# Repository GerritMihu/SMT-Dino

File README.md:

# SMT-Dino
 Blinkender Dinosaurier mit dem 14-Bit Zähler 74HCT4060

## Automatisch generierte Files für Doku mit Kibot

## 0402er LED's als Challenge

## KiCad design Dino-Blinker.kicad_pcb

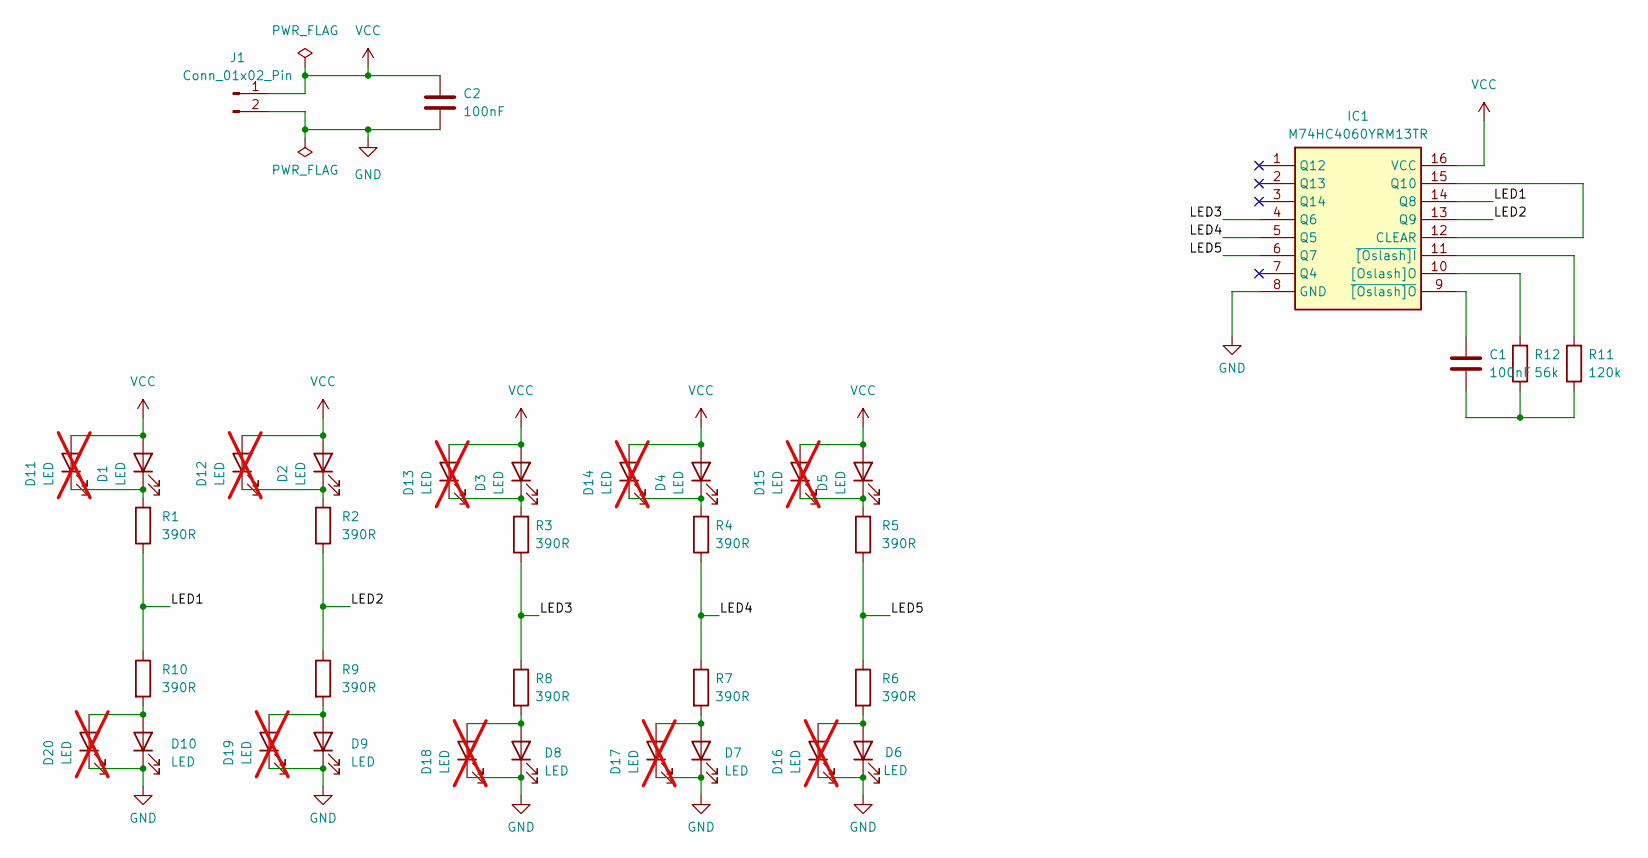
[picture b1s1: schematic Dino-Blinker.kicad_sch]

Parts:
C1, C2: 100nF; C_0805_2012Metric_Pad1.18x1.45mm_HandSolder
D1, D2, D3, D4, D5, D6, D7, D8, D9, D10: LED; LED_0805_2012Metric_Pad1.15x1.40mm_HandSolder
D11, D12, D13, D14, D15, D16, D17, D18, D19, D20: LED; LED_0402_1005Metric_Pad0.77x0.64mm_HandSolder; not fitted
IC1: M74HC4060YRM13TR; SOIC-16_3.9x9.9mm_P1.27mm; Manufacturer_Part_Number M74HC4060YRM13TR; Mouser Part Number 511-M74HC4060YRM13TR
J1: Conn_01x02_Pin; PinHeader_1x02_P2.54mm_Vertical
R1, R2, R3, R4, R5, R6, R7, R8, R9, R10: 390R; R_1206_3216Metric_Pad1.30x1.75mm_HandSolder
R11: 120k; R_1206_3216Metric_Pad1.30x1.75mm_HandSolder
R12: 56k; R_1206_3216Metric_Pad1.30x1.75mm_HandSolder

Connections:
/LED1: IC1.14 (Q8), R1.1, R10.1
/LED2: IC1.13 (Q9), R2.1, R9.1
/LED3: IC1.4 (Q6), R3.1, R8.1
/LED4: IC1.5 (Q5), R4.1, R7.1
/LED5: IC1.6 (Q7), R5.1, R6.1
GND: C2.2, D6.1 (K), D7.1 (K), D8.1 (K), D9.1 (K), D10.1 (K), D16.1 (K), D17.1 (K), D18.1 (K), D19.1 (K), D20.1 (K), IC1.8 (GND), J1.2
unnamed: C1.1, R11.1, R12.1
unnamed: D1.1 (K), D11.1 (K), R1.2
unnamed: D10.2 (A), D20.2 (A), R10.2
unnamed: D2.1 (K), D12.1 (K), R2.2
unnamed: D3.1 (K), D13.1 (K), R3.2
unnamed: D4.1 (K), D14.1 (K), R4.2
unnamed: D5.1 (K), D15.1 (K), R5.2
unnamed: D6.2 (A), D16.2 (A), R6.2
unnamed: D7.2 (A), D17.2 (A), R7.2
unnamed: D8.2 (A), D18.2 (A), R8.2
unnamed: D9.2 (A), D19.2 (A), R9.2
unnamed: IC1.12 (CLEAR), IC1.15 (Q10)
unnamed: IC1.10 ([Oslash]O), R12.2
unnamed: IC1.11 (~[Oslash]I), R11.2
unnamed: C1.2, IC1.9 (~[Oslash]O)
VCC: C2.1, D1.2 (A), D2.2 (A), D3.2 (A), D4.2 (A), D5.2 (A), D11.2 (A), D12.2 (A), D13.2 (A), D14.2 (A), D15.2 (A), IC1.16 (VCC), J1.1

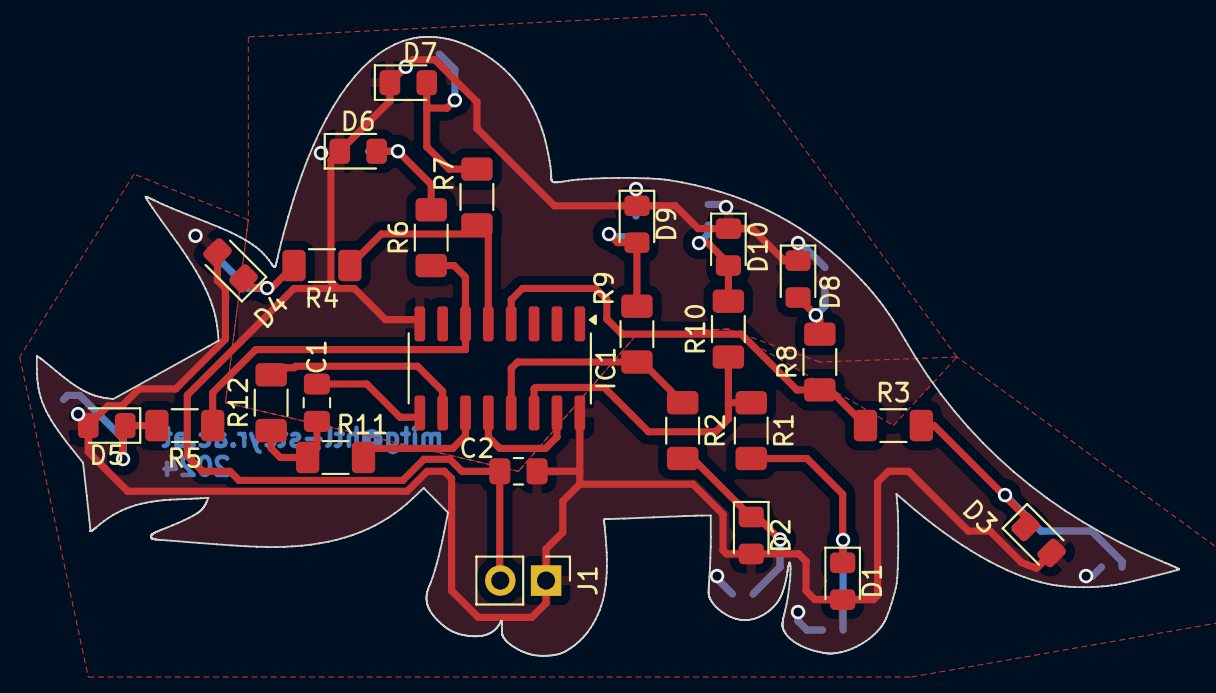
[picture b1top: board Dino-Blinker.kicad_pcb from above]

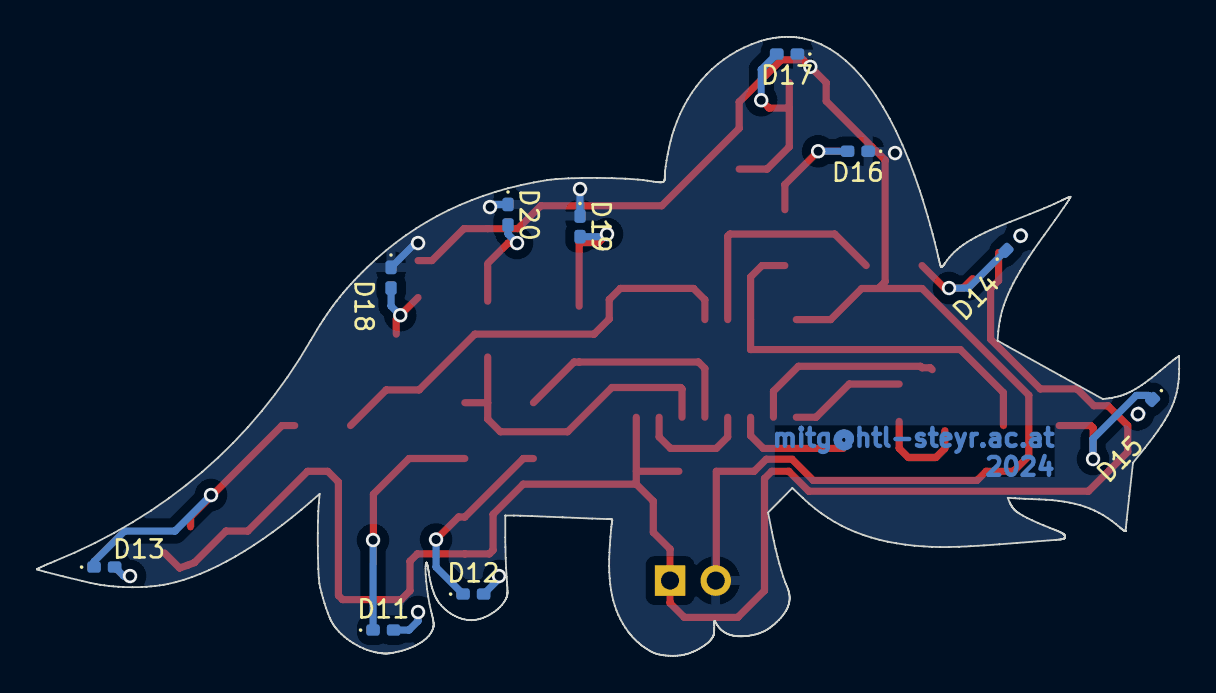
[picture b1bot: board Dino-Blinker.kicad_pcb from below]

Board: 2 copper layers, 63.5 x 34.4 mm, 36 parts (10 on the bottom side), 22 nets.

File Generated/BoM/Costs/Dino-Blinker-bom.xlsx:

|  | KiBot Bill of Materials
 |  | Schematic: | Dino-Blinker | Component Groups: | 7
 |  | Variant: | default | Component Count: | 26 (25 SMD/ 1 THT)
 |  | Revision: |  | Fitted Components: | 26 (25 SMD/ 1 THT)
 |  | Date: | 2024-12-11_00-15-44 | Number of PCBs: | 1
 |  | KiCad Version: | 8.0.6+1 | Total Components: | 26
Row | Description | Part | References | Value | Footprint | Quantity Per PCB | Status | Datasheet | Height | Manufacturer_Name | Manufacturer_Part_Number | Mouser Part Number | Mouser Price/Stock | Arrow Part Number | Arrow Price/Stock
1 |  | C | C1 C2 | 100nF | C_0805_2012Metric_Pad1.18x1.45mm_HandSolder | 2 |  | ~
2 |  | LED | D1 D2 D3 D4 D5 D6 D7 D8 D9 D10 | LED | LED_0805_2012Metric_Pad1.15x1.40mm_HandSolder | 10 |  | ~
3 |  | M74HC4060YRM13TR | IC1 | M74HC4060YRM13TR | SOIC-16_3.9x9.9mm_P1.27mm | 1 |  | http://www.st.com/st-web-ui/static/active/en/resource/techni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 | 1.75 | STMicroelectronics | M74HC4060YRM13TR | 511-M74HC4060YRM13TR | https://www.mouser.co.uk/ProductDetail/STMicroelectronics/M7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 | M74HC4060YRM13TR | https://www.arrow.com/en/products/m74hc4060yrm13tr/stmicroel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
4 |  | Conn_01x02_Pin | J1 | Conn_01x02_Pin | PinHeader_1x02_P2.54mm_Vertical | 1 |  | ~
5 |  | R | R1 R2 R3 R4 R5 R6 R7 R8 R9 R10 | 390R | R_1206_3216Metric_Pad1.30x1.75mm_HandSolder | 10 |  | ~
6 |  | R | R12 | 56k | R_1206_3216Metric_Pad1.30x1.75mm_HandSolder | 1 |  | ~
7 |  | R | R11 | 120k | R_1206_3216Metric_Pad1.30x1.75mm_HandSolder | 1 |  | ~

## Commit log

2024-04-23 Added files
2024-04-23 added QR
2024-05-02 added folder Pics
2024-12-11 run kibot
2024-12-12 edited yaml
2024-12-13 0402er Leds
